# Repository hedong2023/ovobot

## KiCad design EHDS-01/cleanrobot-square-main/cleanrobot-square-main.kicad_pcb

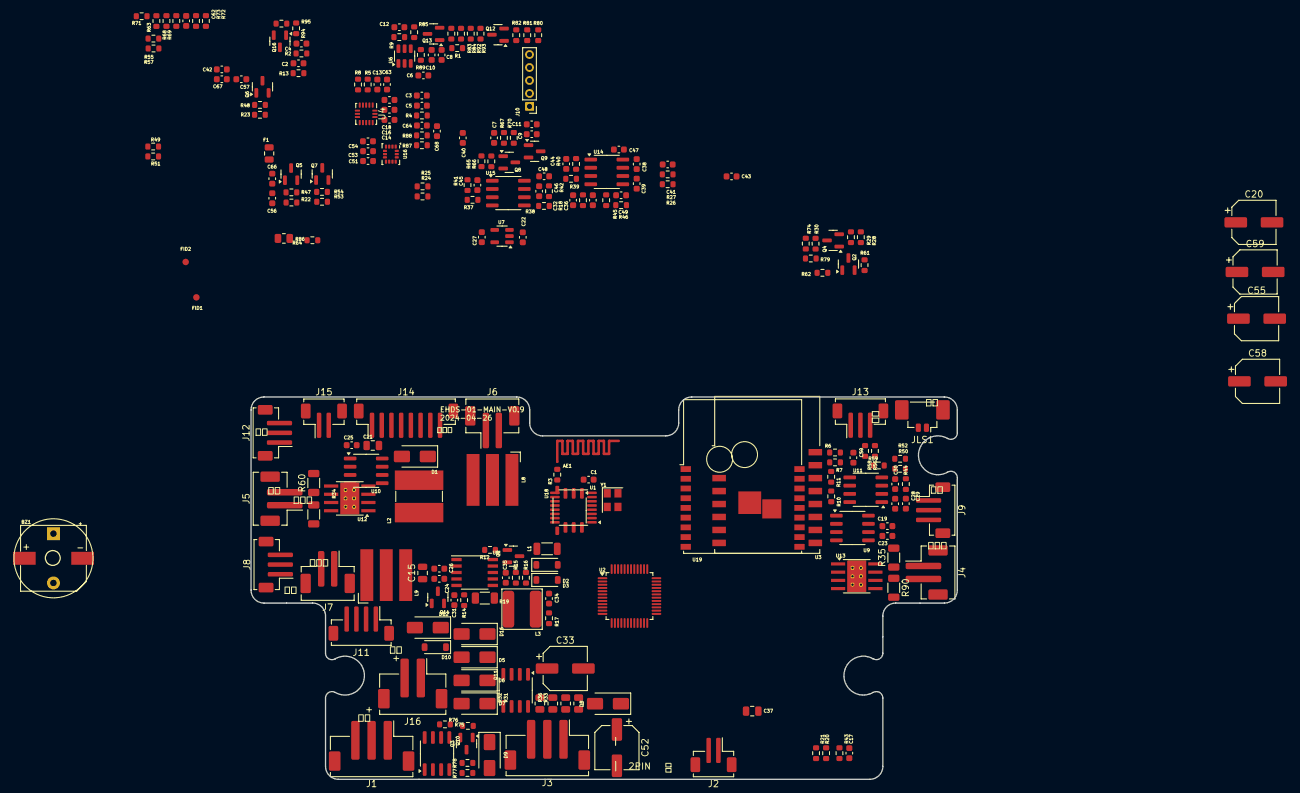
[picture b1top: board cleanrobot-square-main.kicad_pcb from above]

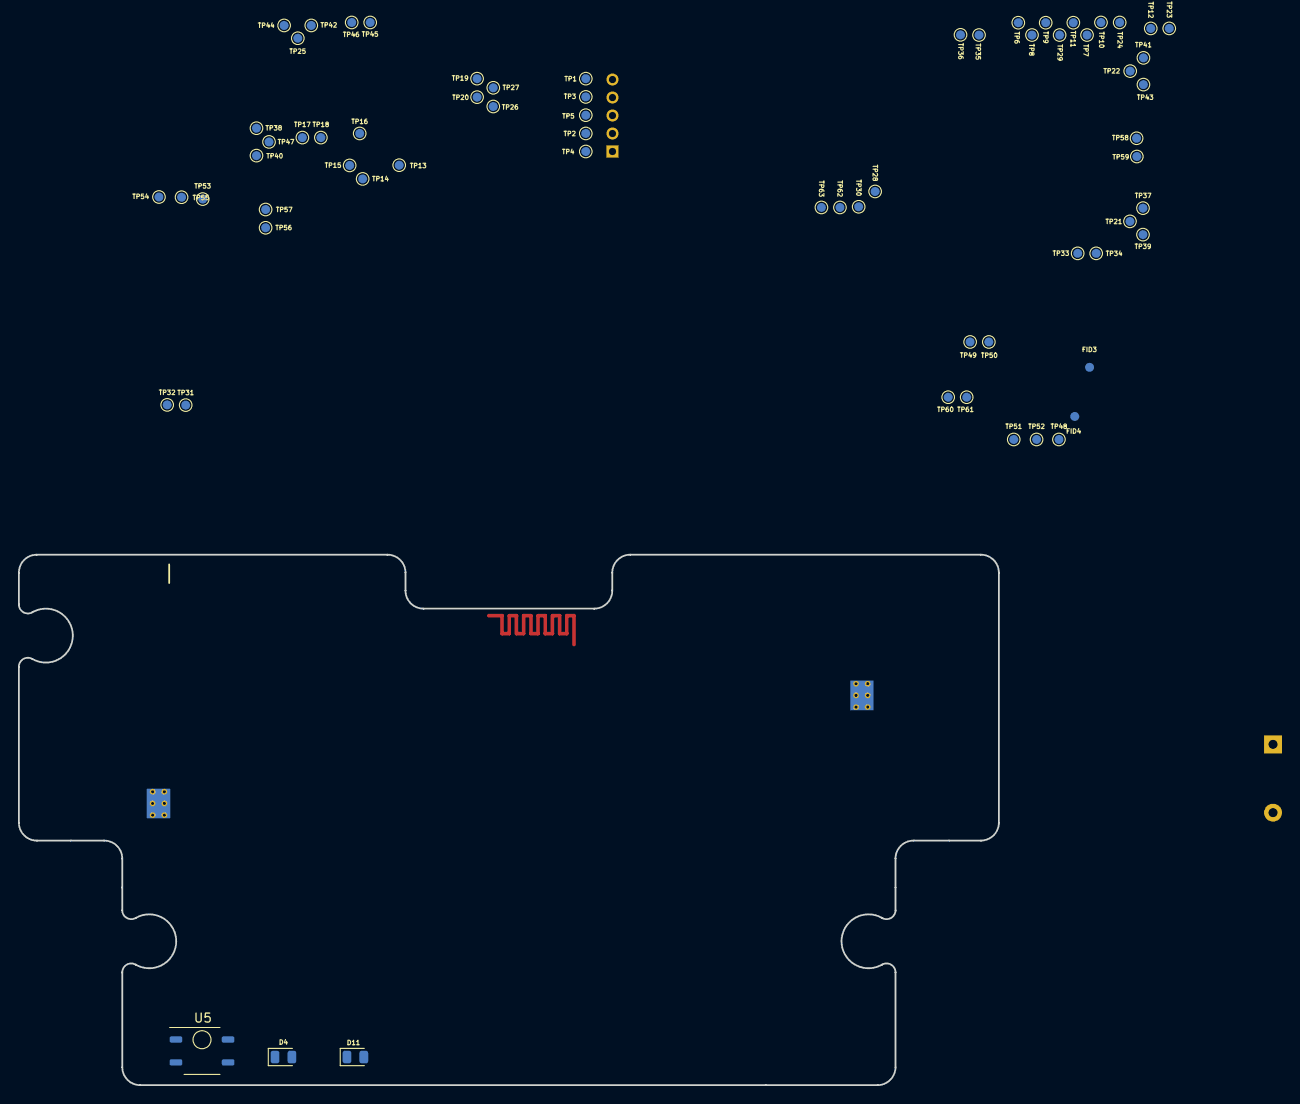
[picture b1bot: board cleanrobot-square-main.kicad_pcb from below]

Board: 2 copper layers, 109.0 x 59.0 mm, 299 parts (68 on the bottom side), 144 nets, no tracks yet.

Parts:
AE1: Antenna; Ovo_PA2401_2.4GHz_Right
BZ1: 85dB/5V; Buzzer_12x9.5RM7.6
BZ2: 85dB/5V 10x9.6x5.5mm; Buzzer_10x9.6x5.5_SMD
C1, C2, C9, C22, C25, C27, C28, C30, C32, C36, C50, C56, C57, C68: 1uF; C_0603_1608Metric
C3, C4, C5, C6, C7, C8, C11, C12, C16, C17, C24, C26, C38, C40, C41, C42, C43, C44, C45, C46, C47, C48, C49, C53, C62, C63, C64, C66, C67: 0.1uF; C_0603_1608Metric
C10: 4.7uF; C_0603_1608Metric
C13, C39, C51: 10nF; C_0603_1608Metric
C14, C29: 0.47uF; C_0603_1608Metric
C15, C21, C37: 10uF/35V; C_0805_2012Metric
C18, C54: 2.2uF; C_0603_1608Metric
C19: 10uF; C_0603_1608Metric
C20, C59: 220uF/10V 6.3x5.4; CP_Elec_6.3x5.4
C23, C34: 1nF; C_0603_1608Metric
C31: 220nF; C_0603_1608Metric
C33, C52, C55, C58: 100uF/35V 6.3x5.4; CP_Elec_6.3x5.4
C35: 1.5pF; C_0603_1608Metric
D1, D5, D6, D7: SS34; D_SMA
D2, D3, D10: SS14; D_SOD-123
D4: BLUE; LED_0805_2012Metric
D8, D9: 1N4004; D_SMA
D11: RED; LED_0805_2012Metric
D12, D16: SMAJ24CA; D_SMA
F1: MF-PSMF050X; Fuse_0805_2012Metric
FID1, FID2, FID3, FID4: Fiducial; Fiducial_1mm_Mask2mm
J1, J3: XH2.54MM/3AWSMT; JST_XHB_B3B-XHB-SM4-TB_1x03-1MP_P2.50mm_Vertical
J2, J15: ZH1.5MM/2ASMT; JST_ZH_B2B-ZR-SM4-TF_1x02-1MP_P1.50mm_Vertical
J4, J5, J6, J7: PH2.0MM/2ASMT; JST_PH_B2B-PH-SM4-TB_1x02-1MP_P2.00mm_Vertical
J8, J9, J12, J13: ZH1.5MM/3ASMT; JST_ZH_B3B-ZR-SM4-TF_1x03-1MP_P1.50mm_Vertical
J10: Conn_01x05; PinHeader_1x05_P2.00mm_Vertical
J11: ZH1.5MM/4ASMT; JST_ZH_B4B-ZR-SM4-TF_1x04-1MP_P1.50mm_Vertical
J14: ZH1.5MM/8ASMT; JST_ZH_B8B-ZR-SM4-TF_1x08-1MP_P1.50mm_Vertical
J16: XHB2.54MM/2ASMT; JST_XHB_B2B-XHB-SM4-TB_1x02-1MP_P2.50mm_Vertical
JLS1: 1.25MM/2ASMT; Molex_PicoBlade_53398-0271_1x02-1MP_P1.25mm_Vertical
L1: 120R@100MHz/3A; L_1206_3216Metric
L2: 68uH; L_GZJ_CD75
L3: 100uH; L_GZJ_WNR6045
L8, L9: 10/500uH; L_WLJ_CD0805
Q1: HSS6107; SOT-23
Q2, Q3, Q4, Q7, Q8, Q9, Q12: SS8050; SOT-23
Q5, Q6: CJ2310; SOT-23
Q10, Q11: NCE4435; SOIC-8_3.9x4.9mm_P1.27mm
Q13, Q16: SI2309; SOT-23
Q14: SI2302; SOT-23
R1, R9, R11, R29, R43, R44, R45, R47, R48, R51, R52, R54, R57, R58, R59, R63, R64, R66, R70, R71, R72, R73, R76, R77, R78, R80, R82, R89, R92, R94: 10K/1%; R_0603_1608Metric
R2, R3, R4, R6, R7, R10, R13, R18, R79, R85: 0R; R_0603_1608Metric
R5, R8: 4.7K/1%; R_0603_1608Metric
R12: 51R; R_0603_1608Metric
R14: 120R; R_0603_1608Metric
R15: 1.5M/1%; R_0603_1608Metric
R16: 120K/1%; R_0603_1608Metric
R17: 100R; R_0603_1608Metric
R19: 0.5R/1%; R_1206_3216Metric
R20, R21, R68, R69: 330R; R_0603_1608Metric
R22, R23, R28, R53, R65, R67, R75, R81: 1K; R_0603_1608Metric
R24, R87: 1M/1%; R_0603_1608Metric
R25, R83, R84, R88: 100K/1%; R_0603_1608Metric
R26: 6.8K/1%; R_0603_1608Metric
R27: 3.3K/1%; R_0603_1608Metric
R30, R74: 680R; R_0603_1608Metric
R31, R32, R33, R36: 0.1R; R_0805_2012Metric
R34, R35, R60, R90: 0.068R/1%(333.333mW); R_1206_3216Metric
R37, R38, R39: 15K/1%; R_0603_1608Metric
R40, R41, R42: 51K/1%; R_0603_1608Metric
R46: 2K/1%; R_0603_1608Metric
R49, R50, R55, R56, R61, R62: 470R; R_0603_1608Metric
R86: 0R; R_0805_2012Metric
R93: 1.6K/1%; R_0603_1608Metric
R95: 30K/5%; R_0603_1608Metric
TP1: RX; TestPoint_Pad_D1.0mm
TP2: SWD; TestPoint_Pad_D1.0mm
TP3: SWC; TestPoint_Pad_D1.0mm
TP4, TP17, TP27, TP29, TP63: 3V3; TestPoint_Pad_D1.0mm
TP5, TP18, TP21, TP22, TP23, TP24, TP25, TP26, TP47, TP48, TP60, TP61, TP62: GND; TestPoint_Pad_D1.0mm
TP6: VPP; TestPoint_Pad_D1.0mm
TP7: LED_RED; TestPoint_Pad_D1.0mm
TP8: CHG_ON_LED; TestPoint_Pad_D1.0mm
TP9: CHG_DONE_LED; TestPoint_Pad_D1.0mm
TP10: IR_OUT; TestPoint_Pad_D1.0mm
TP11: LED_BLUE; TestPoint_Pad_D1.0mm
TP12: START; TestPoint_Pad_D1.0mm
TP13: DO; TestPoint_Pad_D1.0mm
TP14: CLK; TestPoint_Pad_D1.0mm
TP15: DI; TestPoint_Pad_D1.0mm
TP16: CS; TestPoint_Pad_D1.0mm
TP19: RXD; TestPoint_Pad_D1.0mm
TP20: TXD; TestPoint_Pad_D1.0mm
TP28: SCL1; TestPoint_Pad_D1.0mm
TP30: SDA1; TestPoint_Pad_D1.0mm
TP31: WATER_DET_P; TestPoint_Pad_D1.0mm
TP32: WATER_DET_N; TestPoint_Pad_D1.0mm
TP33: SPRAY_BACK_P; TestPoint_Pad_D1.0mm
TP34: SPRAY_BACK_N; TestPoint_Pad_D1.0mm
TP35: SPRAY_FRONT_P; TestPoint_Pad_D1.0mm
TP36: SPRAY_FRONT_N; TestPoint_Pad_D1.0mm
TP37: EDGE_DET_LB_OUT; TestPoint_Pad_D1.0mm
TP38: EDGE_DET_RB; TestPoint_Pad_D1.0mm
TP39: EDGE_DET_LB; TestPoint_Pad_D1.0mm
TP40: EDGE_DET_RB_OUT; TestPoint_Pad_D1.0mm
TP41: EDGE_DET_LT_OUT; TestPoint_Pad_D1.0mm
TP42: EDGE_DET_RT; TestPoint_Pad_D1.0mm
TP43: EDGE_DET_LT; TestPoint_Pad_D1.0mm
TP44: EDGE_DET_RT_OUT; TestPoint_Pad_D1.0mm
TP45: SPEAKER_P; TestPoint_Pad_D1.0mm
TP46: SPEAKER_N; TestPoint_Pad_D1.0mm
TP49, TP50: 24V; TestPoint_Pad_D1.0mm
TP51: BATT; TestPoint_Pad_D1.0mm
TP52: TEMP; TestPoint_Pad_D1.0mm
TP53: VDD; TestPoint_Pad_D1.0mm
TP54: FAN_PWM; TestPoint_Pad_D1.0mm
TP55: FAN_OUT_N; TestPoint_Pad_D1.0mm
TP56: R_MOTOR_OUT+; TestPoint_Pad_D1.0mm
TP57: R_MOTOR_OUT-; TestPoint_Pad_D1.0mm
TP58: L_MOTOR_OUT+; TestPoint_Pad_D1.0mm
TP59: L_MOTOR_OUT-; TestPoint_Pad_D1.0mm
U1: LT8920; TSSOP-16_4.4x5mm_P0.65mm
U2: MM32F0144C6P; LQFP-48_7x7mm_P0.5mm
U3: BT3L; Tuya_BT3L
U4: MPU-6887P; TDK_LGA-16_3x3mm_P0.5mm_LayoutBorder3x5y
U5: IRM-3640CF45; Everlight_IRM-H638T
U6: PMS150C-U06(0xD407B2); SOT-23-6
U7: RT9013-33; SOT-23-5
U8: CN3765; SSOP-10_3.9x4.9mm_P1.00mm
U9: WT588F02B-8S-B2(EHDS-01); SOIC-8_3.9x4.9mm_P1.27mm
U10: XL1509-5.0E1; SOIC-8_3.9x4.9mm_P1.27mm
U11: 8002A; SOIC-8_3.9x4.9mm_P1.27mm
U12, U13: DRV8870DDAR; Texas_HTSOP-8-1EP_3.9x4.9mm_P1.27mm_EP2.95x4.9mm_Mask2.4x3.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
U14, U15: LMV358TP-SR; SOIC-8_3.9x4.9mm_P1.27mm
U16: LSM6DSR; LGA-14_3x2.5mm_P0.5mm_LayoutBorder3x4y
U18: GH6220B; SOIC-8_3.9x4.9mm_P1.27mm
U19: WBR1; Tuya_WBR1
Y1: 12MHz/22pF(10ppm); Oscillator_SMD_Abracon_ASE-4Pin_3.2x2.5mm

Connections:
+3.3VA: C36.1, C47.1, C48.1, R18.2, R45.1, U14.8 (V+), U15.8 (V+)
+3.3VDAC: C4.1, R2.2, U1.12 (LDO_IN), U18.8 (VDD)
+3.3VP: C2.1, C9.1, C11.1, R2.1, R13.2, R80.2, U3.8 (VDD_BAT), U19.1 (VCC), U19.4 (3V3)
+3V3: C6.2, C7.2, C8.2, C10.2, C12.1, C13.2, C16.2, C17.1, C18.2, C19.1, C27.1, C32.1, C51.2, C53.2, C54.2, C62.1, D4.2 (A), D11.2 (A), J10.1, J11.1, J14.4, Q2.3 (C), R4.2, R5.2, R8.2, R9.1, R13.1, R18.1, R26.1, R43.1, R49.1, R50.1, R51.1, R52.1, R55.1, R56.1, R57.1, R58.1, R62.1, R63.2, R64.1, R71.1, R89.1, TP4.1, TP17.1, TP27.1, TP29.1, TP63.1, U2.1 (VDD), U2.24 (VDD), U2.48 (VDD), U4.1 (VDDIO), U4.5 (CS), U4.16 (VDD), U5.3 (Vs), U6.5 (VDD), U7.5 (VOUT), U9.6 (VDD), U16.5 (VDDIO), U16.8 (VDD), U16.12 (CS)
+5V: BZ1.1 (-), BZ2.1 (-), C20.1, C22.1, C50.1, F1.1, L2.2, U7.1 (VIN), U7.3 (EN), U10.3 (FB), U11.6 (VDD)
+24V: D5.2 (A), D6.2 (A), D10.2 (A), J16.1, TP49.1, TP50.1
+BATT: J1.3, Q10.1 (S), Q10.2 (S), Q10.3 (S), R77.2, TP51.1
/driver/L_MOTOR_OUT+: J5.1, TP58.1, U12.6 (OUT1)
/driver/L_MOTOR_OUT-: J5.2, TP59.1, U12.8 (OUT2)
/driver/R_MOTOR_OUT+: J4.1, TP56.1, U13.6 (OUT1)
/driver/R_MOTOR_OUT-: J4.2, TP57.1, U13.8 (OUT2)
/driver/VREF55: C38.1, C39.1, U14.3 (+), U14.6 (-), U14.7, U15.3 (+), U15.5 (+)
/main/6220_ANT: R3.1, U1.9 (ANTB), U18.4 (ANT)
/main/6220_XC1: U1.7 (XTALI), U18.1 (XC1), Y1.1
/main/6220_XC2: U1.6 (XTALO), U18.2 (XC2), Y1.3
/main/BLE_MCU_RXD: R6.2, U2.43 (PB7)
/main/BLE_MCU_TXD: R7.2, U2.42 (PB6)
/main/MISO: U1.2 (MISO), U2.40 (PB4)
/main/MOSI: U1.1 (MOSI), U2.41 (PB5), U18.7 (DATA/MOSI)
/main/RF_REST: U1.4 (~RST), U2.6 (PF1)
/main/SCK: U1.16 (SCK), U2.39 (PB3), U18.6 (SCK)
/main/SCS: U1.14 (SS), U2.5 (PF0), U18.5 (CSN)
/main/TSD_DATA: U2.3 (PC14), U6.3 (PA6)
/main/WIFI_MCU_RXD: R6.1, TP19.1, U3.16 (TL_B1), U19.2 (TX)
/main/WIFI_MCU_TXD: R7.1, TP20.1, U3.15 (TL_B7), U19.3 (RX)
/peripheral/BLUE: Q9.3 (C), R21.1, R69.1
/peripheral/CHG_ON_LED_K: J14.2, Q16.2 (S), TP8.1
/peripheral/RED: Q8.3 (C), R20.1, R68.1
/peripheral/VOICE_BUSY: R11.1, TP16.1, U9.1 (PC2/CS)
/power/BATT_CHRG: C35.1, C37.1, D7.2 (A), Q10.5 (D), Q10.6 (D), Q10.7 (D), Q10.8 (D), R15.1, R19.2, R87.1, U8.7 (BAT)
ADC_BATT: C64.1, R87.2, R88.1, U2.10 (PA0)
ADC_FAN_MOTOR: C44.2, R40.2, U2.11 (PA1), U14.1
ADC_LEFT_MOTOR: C45.2, R41.2, U2.15 (PA5), U15.1
ADC_RIGHT_MOTOR: C46.2, R42.2, U2.16 (PA6), U15.7
ADC_VDD: C40.1, R24.2, R25.1, U2.17 (PA7)
BATT_ON: R75.2, U2.21 (PB10)
BELL: R53.1, U2.20 (PB2)
CHG_DONE_LED: J14.3, R73.1, TP9.1
CHG_ON_LED: R72.1, R95.1
CHRG_LED: R92.2, R93.2, U2.33 (PA12)
EDGE_DET_LB: J8.3, R51.2, TP39.1, U2.35 (PF6)
EDGE_DET_LT: J12.3, R57.2, TP43.1, U2.36 (PF7)
EDGE_DET_RB: J9.3, R52.2, TP38.1, U2.27 (PB14)
EDGE_DET_RT: J13.3, R58.2, TP42.1, U2.28 (PB15)
EN_CHRG: Q14.1 (G), R89.2, U6.4 (PA5/~PRSTB)
GND: C1.2, C2.2, C3.1, C4.2, C5.1, C6.1, C7.1, C8.1, C9.2, C10.1, C11.2, C12.2, C13.1, C14.1, C15.2, C16.1, C17.2, C18.1, C19.2, C20.2, C21.2, C22.2, C23.2, C24.2, C25.2, C27.2, C28.2, C30.1, C31.2, C32.2, C33.2, C34.2, C36.2, C37.2, C38.2, C39.2, C40.2, C41.2, C42.2, C43.2, C47.2, C48.2, C49.2, C50.2, C51.1, C52.2, C53.1, C54.1, C55.2, C58.2, C62.2, C63.2, C64.2, C68.2, D1.2 (A), D3.2 (A), D9.2 (A), D12.2 (A), D16.2 (A), J1.1, J1.MP (MountPin), J2.MP (MountPin), J3.MP (MountPin), J4.MP (MountPin), J5.MP (MountPin), J8.2, J8.MP (MountPin), J9.2, J9.MP (MountPin), J10.3, J11.4, J11.MP (MountPin), J12.2, J12.MP (MountPin), J13.2, J13.MP (MountPin), J14.8, J14.MP (MountPin), J15.2, J15.MP (MountPin), J16.2, J16.MP (MountPin), JLS1.MP (MountPin), Q3.2 (E), Q4.2 (E), Q7.2 (E), Q8.2 (E), Q9.2 (E), Q12.2 (E), Q14.2 (S), R1.1, R16.2, R25.2, R27.2, R29.1, R31.2, R32.2, R33.2, R34.2, R35.2, R36.2, R46.2, R54.2, R60.2, R61.2, R66.2, R70.2, R76.1, R82.2, R86.1, R88.2, R90.2, R93.1, TP5.1, TP18.1, TP21.1, TP22.1, TP23.1, TP24.1, TP25.1, TP26.1, TP47.1, TP48.1, TP60.1, TP61.1, TP62.1, U1.15 (VSS), U2.8 (VSSA), U2.23 (VSS), U2.47 (VSS), U3.9 (GND), U3.17 (PAD), U4.4 (AD0/SDO), U4.9 (RESV), U4.10 (RESV), U4.11 (RESV), U4.12 (RESV), U4.13 (GND), U4.15 (RECV), U5.2 (GND), U6.2 (GND), U7.2 (GND), U8.2 (GND), U9.8 (GND), U10.4 (EN), U10.5 (GND), U10.6 (GND), U10.7 (GND), U10.8 (GND), U11.7 (GND), U12.1 (GND), U12.9 (GND), U13.1 (GND), U13.9 (GND), U14.4 (V-), U15.4 (V-), U16.1 (SDO/SA0), U16.2 (SDX), U16.3 (SCX), U16.6 (GND), U16.7 (GND), U18.3 (VSS), U19.5 (GND), U19.14 (GND), U19.15 (GND), U19.18 (GND), U19.19 (PAD), Y1.2, Y1.4
GNDA: C56.2, C57.2, C59.2, C66.2, C67.2, J6.MP (MountPin), J7.MP (MountPin), Q5.2 (S), Q6.2 (S), R47.2, R48.2, R86.2
IR_OUT: J14.7, R43.2, R63.1, TP10.1, U2.18 (PB0), U5.1 (OUT)
LED_BLUE: R67.1, U2.25 (PB12)
LED_RED: R65.1, U2.22 (PB11)
unnamed: AE1.1 (A), R3.2
unnamed: BZ1.2 (+), BZ2.2 (+), Q7.3 (C)
unnamed: C29.2, R44.1
unnamed: C31.1, R14.2
unnamed: C34.1, R17.2
unnamed: C56.1, C57.1, C59.1, C66.1, C67.1, F1.2, L8.1, L9.1
unnamed: D1.1 (K), L2.1, U10.2 (OUT)
unnamed: D2.2 (A), L1.2
unnamed: D2.1 (K), D3.1 (K), L3.1, R17.1
unnamed: D4.1 (K), R21.2
unnamed: D8.2 (A), J3.2, R31.1, R32.1, R33.1, R36.1, R39.1, TP55.1
unnamed: D9.1 (K), J3.3, Q11.5 (D), Q11.6 (D), Q11.7 (D), Q11.8 (D), R79.2, TP54.1
unnamed: D11.1 (K), R20.2
unnamed: J2.1, R62.2, TP31.1
unnamed: J2.2, Q2.1 (B), TP32.1
unnamed: J6.1, L8.2, Q5.3 (D), TP34.1
unnamed: J6.2, L8.3, TP33.1
unnamed: J7.1, L9.2, Q6.3 (D), TP36.1
unnamed: J7.2, L9.3, TP35.1
unnamed: J8.1, R49.2, TP37.1
unnamed: J9.1, R50.2, TP40.1
unnamed: J12.1, R55.2, TP41.1
unnamed: J13.1, R56.2, TP44.1
unnamed: J14.5, R69.2, TP11.1
unnamed: J14.6, R68.2, TP7.1
unnamed: JLS1.1, TP46.1, U11.8 (VO2)
unnamed: JLS1.2, R59.2, TP45.1, U11.5 (VO1)
unnamed: L1.1, Q1.3 (D)
unnamed: Q1.1 (G), R12.1
unnamed: Q3.1 (B), R75.1, R76.2
unnamed: Q3.3 (C), R78.1
unnamed: Q4.1 (B), R28.2, R29.2
unnamed: Q4.3 (C), R30.2, R79.1
unnamed: Q5.1 (G), R22.2, R47.1
unnamed: Q6.1 (G), R23.2, R48.1
unnamed: Q7.1 (B), R53.2, R54.1
unnamed: Q8.1 (B), R65.2, R66.1
unnamed: Q9.1 (B), R67.2, R70.1
unnamed: Q10.4 (G), R77.1, R78.2
unnamed: Q11.4 (G), R30.1, R74.2
unnamed: Q12.1 (B), R81.2, R82.1
unnamed: Q12.3 (C), R84.1
unnamed: Q13.1 (G), R83.1, R84.2
unnamed: Q14.3 (D), R14.1, U8.5 (COM)
unnamed: Q16.3 (D), R92.1
unnamed: Q16.1 (G), R94.1, R95.2
unnamed: C1.1, U1.5 (LDO_OUT), U1.8 (PLL_VDD)
unnamed: R1.2, U2.44 (BOOT0)
unnamed: C3.2, U2.7 (NRST)
unnamed: C5.2, R4.1, U2.9 (VDDA)
unnamed: R80.1, U3.3 (EN)
unnamed: C14.2, U4.14 (REGOUT)
unnamed: R9.2, U6.6 (PA3)
unnamed: L3.2, R19.1, U8.8 (CSP)
unnamed: R12.2, U8.10 (DRV)
unnamed: C35.2, R15.2, R16.1, U8.6 (FB)
unnamed: C26.2, U8.1 (VG)
unnamed: R72.2, U8.3 (~CHRG)
unnamed: R73.2, U8.4 (~DONE)
unnamed: R10.2, U9.2 (PC1/SO)
unnamed: TP15.1, U9.3 (PI0/SI)
unnamed: TP14.1, U9.4 (PI1/SCK)
unnamed: C23.1, U9.5 (PWMN)
unnamed: C29.1, U9.7 (PWMP/DAC)
unnamed: C30.2, U11.2 (BYPASS), U11.3 (IN+)
unnamed: R44.2, R59.1, U11.4 (IN-)
unnamed: C28.1, R11.2, U11.1 (~SD)
unnamed: R34.1, R37.1, R60.1, U12.7 (ISEN)
unnamed: C41.1, R26.2, R27.1, U12.4 (VREF), U13.4 (VREF)
unnamed: R35.1, R38.1, R90.1, U13.7 (ISEN)
unnamed: C44.1, R39.2, R40.1, U14.2 (-)
unnamed: C49.1, R45.2, R46.1, U14.5 (+)
unnamed: C45.1, R37.2, R41.1, U15.2 (-)
unnamed: C46.1, R38.2, R42.1, U15.6 (-)
PWM_FAN: R28.1, U2.14 (PA4)
PWM_LEFT1: U2.29 (PA8), U12.3 (IN1)
PWM_LEFT2: U2.30 (PA9), U12.2 (IN2)
PWM_RIGHT1: U2.31 (PA10), U13.3 (IN1)
PWM_RIGHT2: U2.32 (PA11), U13.2 (IN2)
SCL1: J11.2, R5.1, TP28.1, U2.45 (PB8), U4.2 (SCL/SCLK), U16.13 (SCL)
SDA1: J11.3, R8.1, TP30.1, U2.46 (PB9), U4.3 (SDA/SDI), U16.14 (SDA)
SPRAY_BACK: R22.1, U2.13 (PA3)
SPRAY_FRONT: R23.1, U2.12 (PA2)
START: J15.1, R71.2, TP12.1, U2.2 (PC13)
SWCLK: J10.4, TP3.1, U2.37 (PA14)
SWDIO: J10.2, TP2.1, U2.34 (PA13)
SW_LED_POWER: R81.1, U2.26 (PB13)
TEMP: C63.1, J1.2, R64.2, TP52.1, U6.1 (PA4)
UART2_RX: J10.5, TP1.1, U2.38 (PA15)
VCC: C15.1, C24.1, C26.1, D10.1 (K), D12.1 (K), Q1.2 (S), Q13.2 (S), R83.2, R85.2, U8.9 (VCC)
VDD: C21.1, C25.1, C33.1, C42.1, C43.1, C52.1, C55.1, C58.1, D5.1 (K), D6.1 (K), D7.1 (K), D8.1 (K), D16.1 (K), J3.1, Q11.1 (S), Q11.2 (S), Q11.3 (S), R24.1, R74.1, TP53.1, U10.1 (VIN), U12.5 (VM), U13.5 (VM)
VOICE_DATA: R10.1, TP13.1, U2.4 (PC15)
VPP: J14.1, Q13.3 (D), R85.1, R94.2, TP6.1
WATER_DET: C68.1, Q2.2 (E), R61.1, U2.19 (PB1)

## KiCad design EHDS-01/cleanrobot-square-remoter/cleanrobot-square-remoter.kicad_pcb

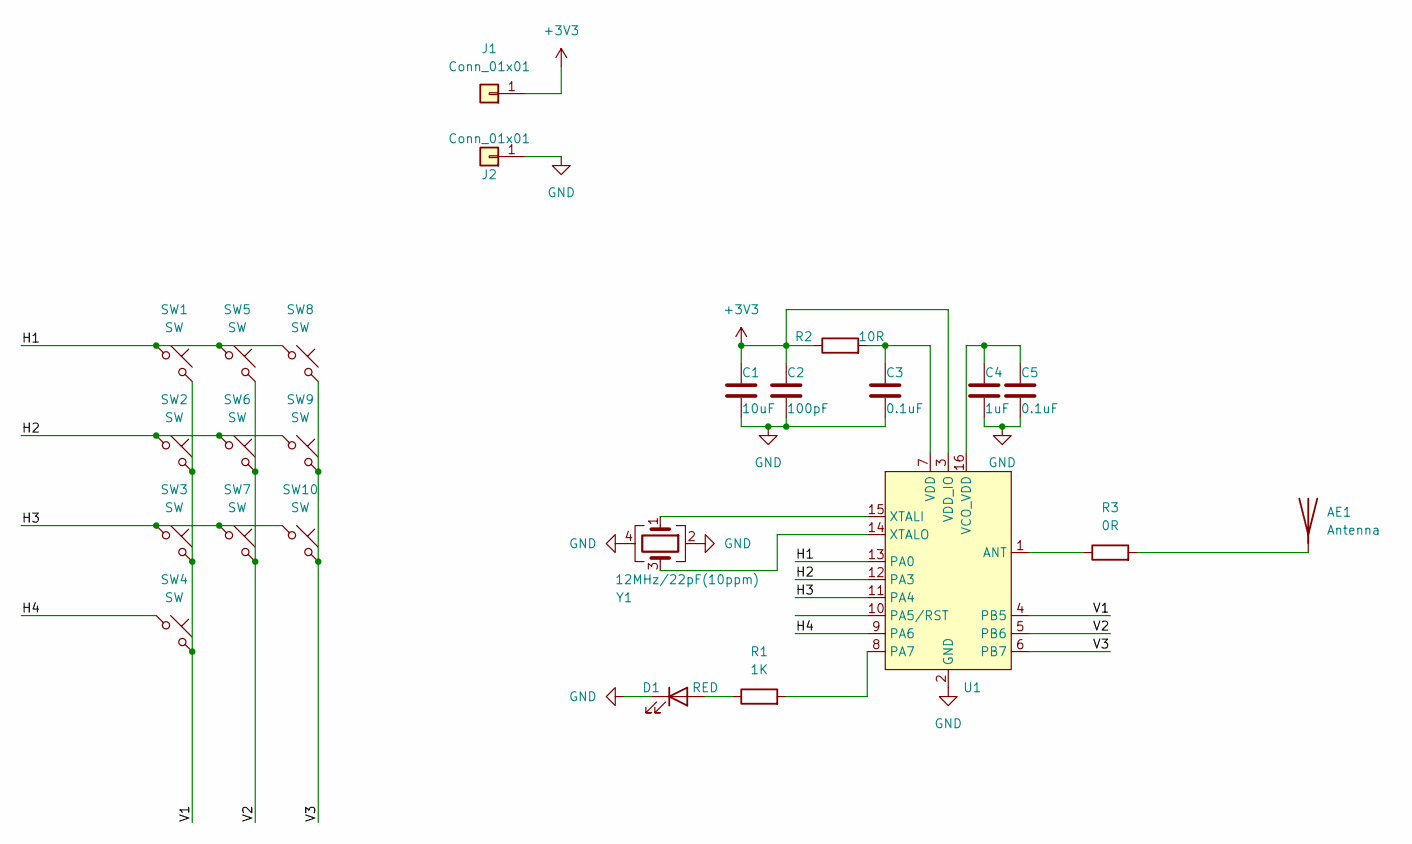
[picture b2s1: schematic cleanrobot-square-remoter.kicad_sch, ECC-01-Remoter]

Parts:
AE1: Antenna; Ovo_PA2401_2.4GHz_Left
C1: 10uF; C_0603_1608Metric
C2: 100pF; C_0603_1608Metric
C3, C5: 0.1uF; C_0603_1608Metric
C4: 1uF; C_0603_1608Metric
D1: RED; LED_D5.0mm
J1, J2: Conn_01x01; Pad_THTPad_4.3x2.1mm_Drill3.1x0.9mm
R1: 1K; R_0603_1608Metric
R2: 10R; R_0603_1608Metric
R3: 0R; R_0603_1608Metric
SW1, SW2, SW3, SW4, SW5, SW6, SW7, SW8, SW9, SW10: SW; Dome_SLICE_6x6mm
U1: SOP-16_3.9x9.9mm_P1.27mm
Y1: 12MHz/22pF(10ppm); Oscillator_SMD_Abracon_ASE-4Pin_3.2x2.5mm

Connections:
+3V3: C1.1, C2.1, J1.1, R2.1, U1.3 (VDD_IO)
/H1: SW1.1, SW5.1, SW8.1, U1.13 (PA0)
/H2: SW2.1, SW6.1, SW9.1, U1.12 (PA3)
/H3: SW3.1, SW7.1, SW10.1, U1.11 (PA4)
/H4: SW4.1, U1.9 (PA6)
/V1: SW1.2, SW2.2, SW3.2, SW4.2, U1.4 (PB5)
/V2: SW5.2, SW6.2, SW7.2, U1.5 (PB6)
/V3: SW8.2, SW9.2, SW10.2, U1.6 (PB7)
GND: C1.2, C2.2, C3.2, C4.2, C5.2, D1.1 (K), J2.1, U1.2 (GND), Y1.2, Y1.4
unnamed: AE1.1 (A), R3.2
unnamed: C3.1, R2.2, U1.7 (VDD)
unnamed: C4.1, C5.1, U1.16 (VCO_VDD)
unnamed: D1.2 (A), R1.1
unnamed: R1.2, U1.8 (PA7)
unnamed: R3.1, U1.1 (ANT)
unnamed: U1.14 (XTALO), Y1.3
unnamed: U1.15 (XTALI), Y1.1

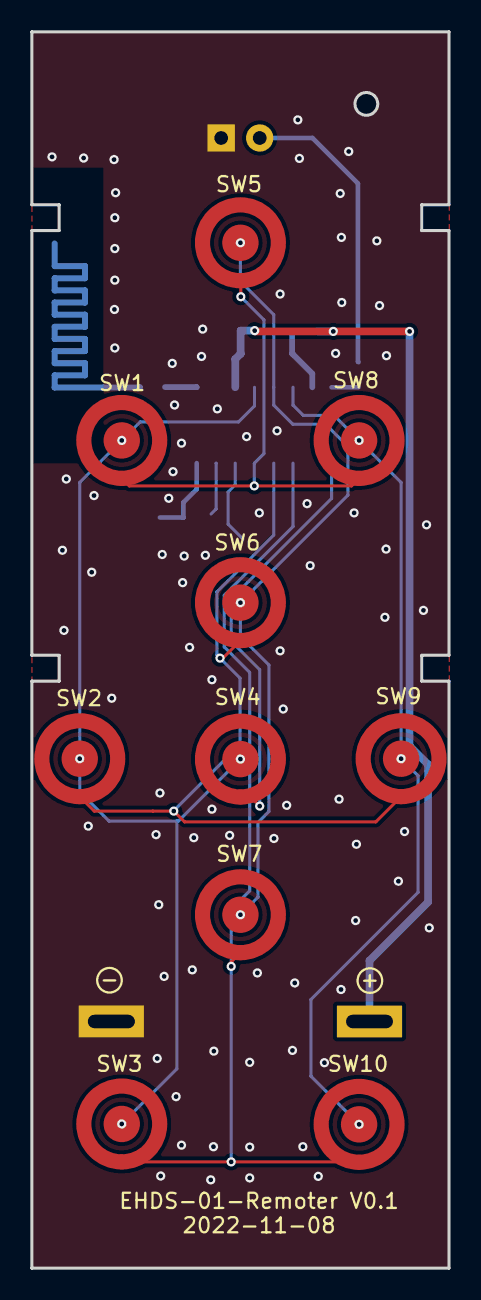
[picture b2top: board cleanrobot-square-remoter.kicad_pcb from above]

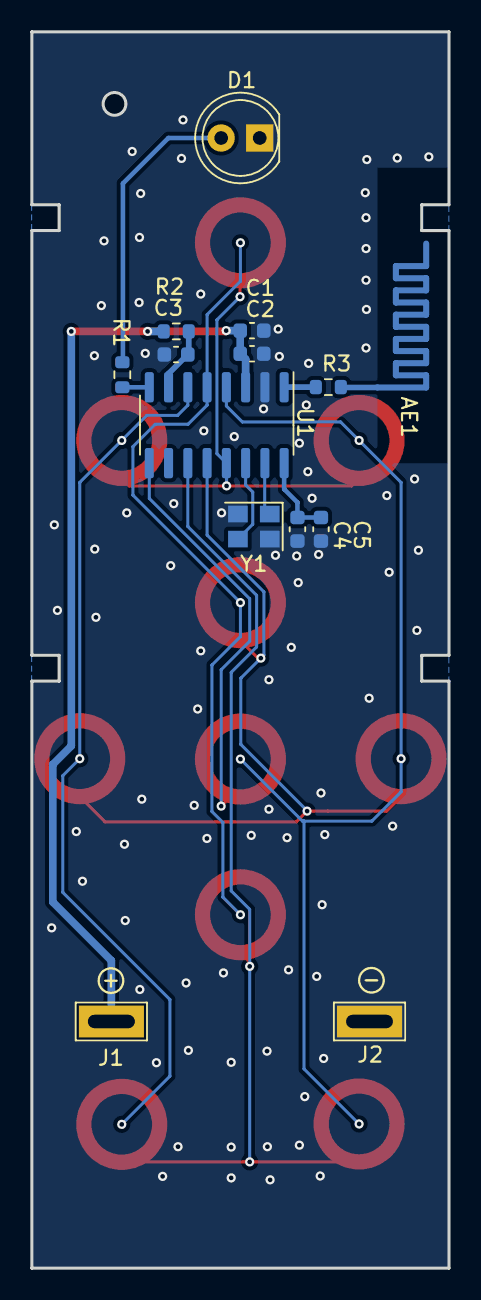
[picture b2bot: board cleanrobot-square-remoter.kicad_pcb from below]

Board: 2 copper layers, 27.5 x 81.5 mm, 24 parts (14 on the bottom side), 17 nets.

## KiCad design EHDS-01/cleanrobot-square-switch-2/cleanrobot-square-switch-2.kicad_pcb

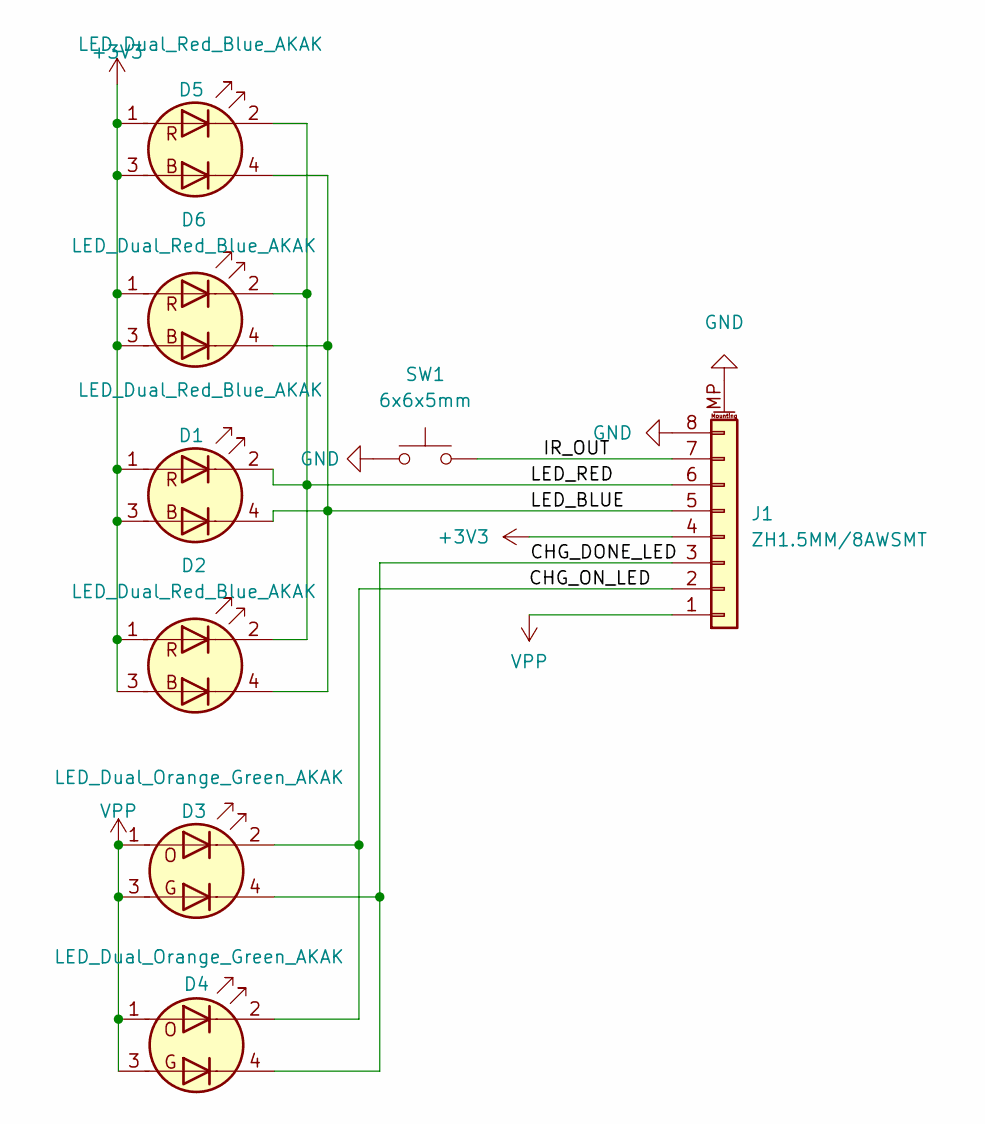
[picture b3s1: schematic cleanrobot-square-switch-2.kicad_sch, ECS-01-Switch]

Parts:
D1, D2, D5, D6: LED_Dual_Red_Blue_AKAK; LED_Dual_1.6x1.5mm
D3, D4: LED_Dual_Orange_Green_AKAK; LED_Dual_1.6x1.5mm
J1: ZH1.5MM/8AWSMT; JST_ZH_S8B-ZR-SM4-TF_1x08-1MP_P1.50mm_Horizontal
SW1: 6x6x5mm; SW_Push_1P1T_NO_6x6mm_H9.5mm

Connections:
+3V3: D1.1 (A1), D1.3 (A2), D2.1 (A1), D2.3 (A2), D5.1 (A1), D5.3 (A2), D6.1 (A1), D6.3 (A2), J1.4
/CHG_DONE_LED: D3.4 (K2), D4.4 (K2), J1.3
/CHG_ON_LED: D3.2 (K1), D4.2 (K1), J1.2
/IR_OUT: J1.7, SW1.2
/LED_BLUE: D1.4 (K2), D2.4 (K2), D5.4 (K2), D6.4 (K2), J1.5
/LED_RED: D1.2 (K1), D2.2 (K1), D5.2 (K1), D6.2 (K1), J1.6
GND: J1.8, J1.MP (MountPin), SW1.1
VPP: D3.1 (A1), D3.3 (A2), D4.1 (A1), D4.3 (A2), J1.1

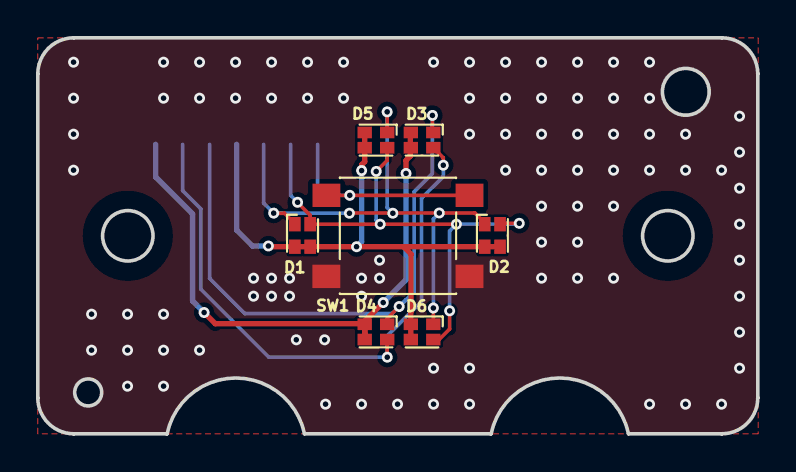
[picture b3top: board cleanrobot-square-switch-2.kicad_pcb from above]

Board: 2 copper layers, 40.0 x 22.0 mm, 8 parts (1 on the bottom side), 8 nets.

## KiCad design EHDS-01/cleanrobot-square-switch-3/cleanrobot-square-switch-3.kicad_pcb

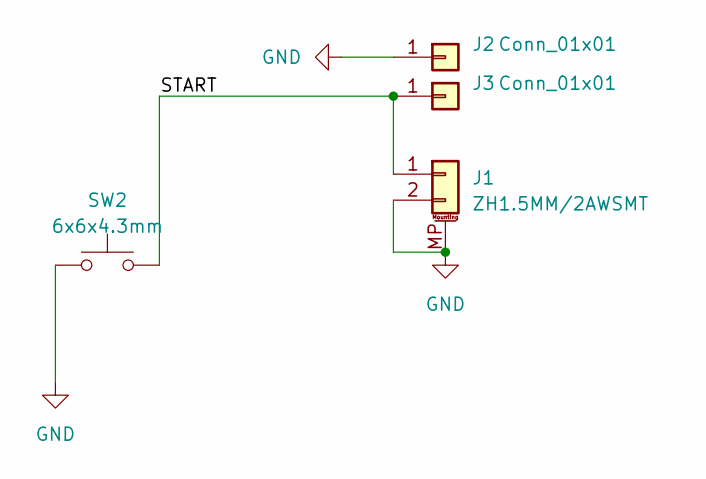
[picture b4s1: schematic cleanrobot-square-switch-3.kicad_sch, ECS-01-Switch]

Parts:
J1: ZH1.5MM/2AWSMT; JST_ZH_S2B-ZR-SM4-TF_1x02-1MP_P1.50mm_Horizontal
J2, J3: Conn_01x01; SolderWire-0.5sqmm_1x01_D0.9mm_OD2.1mm
SW2: 6x6x4.3mm; SW_Push_1P1T_NO_6x6mm_H9.5mm

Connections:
/START: J1.1, J3.1, SW2.2
GND: J1.2, J1.MP (MountPin), J2.1, SW2.1

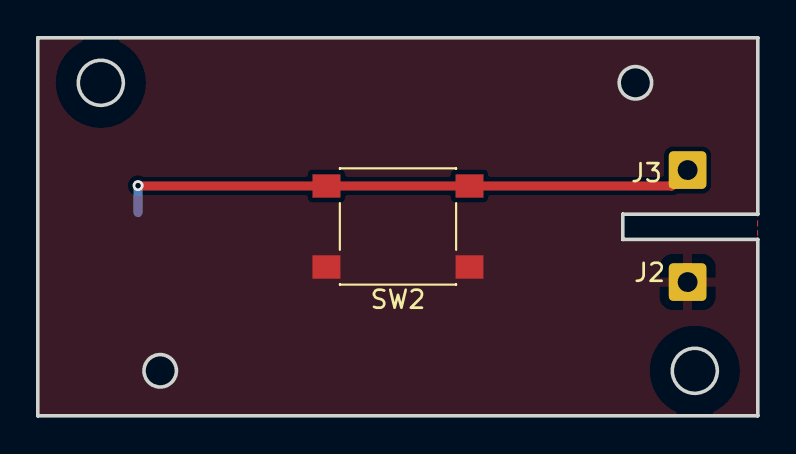
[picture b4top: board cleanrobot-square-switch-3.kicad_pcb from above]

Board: 2 copper layers, 40.0 x 21.0 mm, 4 parts (1 on the bottom side), 2 nets.

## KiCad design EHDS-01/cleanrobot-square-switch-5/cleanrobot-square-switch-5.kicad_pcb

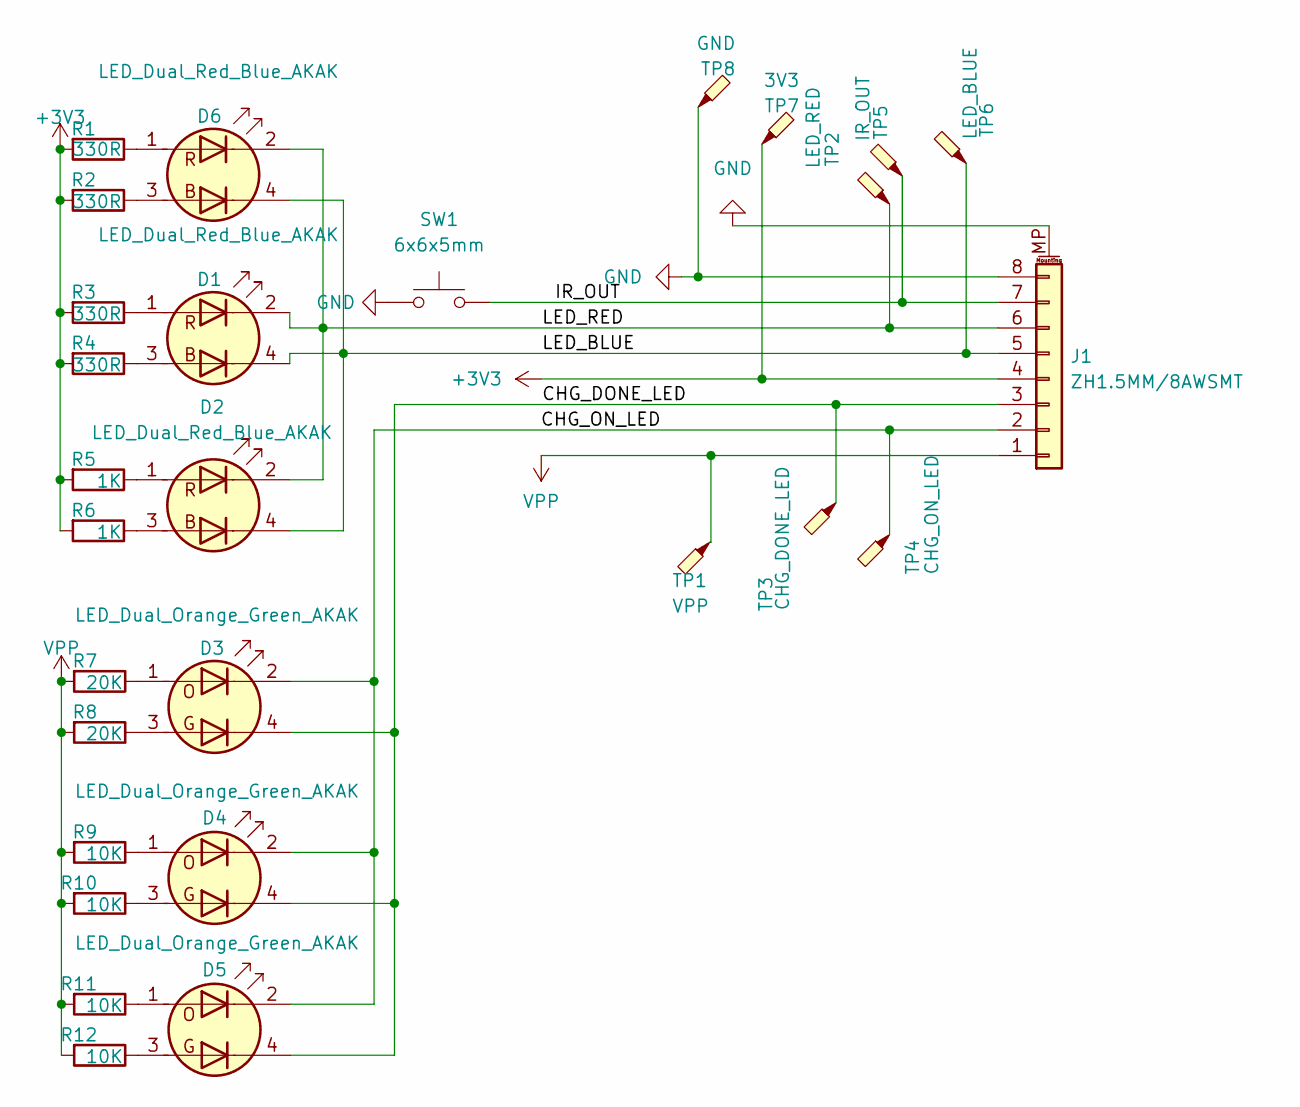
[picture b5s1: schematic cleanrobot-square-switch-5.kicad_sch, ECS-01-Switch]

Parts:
D1, D2, D6: LED_Dual_Red_Blue_AKAK; LED_Dual_1.6x1.5mm
D3, D4, D5: LED_Dual_Orange_Green_AKAK; LED_Dual_1.6x1.5mm
J1: ZH1.5MM/8AWSMT; JST_ZH_S8B-ZR-SM4-TF_1x08-1MP_P1.50mm_Horizontal
R1, R2, R3, R4: 330R; R_0603_1608Metric
R5, R6: 1K; R_0603_1608Metric
R7, R8: 20K; R_0603_1608Metric
R9, R10, R11, R12: 10K; R_0603_1608Metric
SW1: 6x6x5mm; SW_Push_1P1T_NO_6x6mm_H5.0mm
TP1: VPP; TestPoint_Pad_D1.0mm
TP2: LED_RED; TestPoint_Pad_D1.0mm
TP3: CHG_DONE_LED; TestPoint_Pad_D1.0mm
TP4: CHG_ON_LED; TestPoint_Pad_D1.0mm
TP5: IR_OUT; TestPoint_Pad_D1.0mm
TP6: LED_BLUE; TestPoint_Pad_D1.0mm
TP7: 3V3; TestPoint_Pad_D1.0mm
TP8: GND; TestPoint_Pad_D1.0mm

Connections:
+3V3: J1.4, R1.2, R2.2, R3.2, R4.2, R5.2, R6.2, TP7.1
/CHG_DONE_LED: D3.4 (K2), D4.4 (K2), D5.4 (K2), J1.3, TP3.1
/CHG_ON_LED: D3.2 (K1), D4.2 (K1), D5.2 (K1), J1.2, TP4.1
/IR_OUT: J1.7, SW1.2, TP5.1
/LED_BLUE: D1.4 (K2), D2.4 (K2), D6.4 (K2), J1.5, TP6.1
/LED_RED: D1.2 (K1), D2.2 (K1), D6.2 (K1), J1.6, TP2.1
GND: J1.8, J1.MP (MountPin), SW1.1, TP8.1
unnamed: D1.1 (A1), R3.1
unnamed: D1.3 (A2), R4.1
unnamed: D2.1 (A1), R5.1
unnamed: D2.3 (A2), R6.1
unnamed: D3.1 (A1), R7.1
unnamed: D3.3 (A2), R8.1
unnamed: D4.1 (A1), R9.1
unnamed: D4.3 (A2), R10.1
unnamed: D5.1 (A1), R11.1
unnamed: D5.3 (A2), R12.1
unnamed: D6.1 (A1), R1.1
unnamed: D6.3 (A2), R2.1
VPP: J1.1, R7.2, R8.2, R9.2, R10.2, R11.2, R12.2, TP1.1

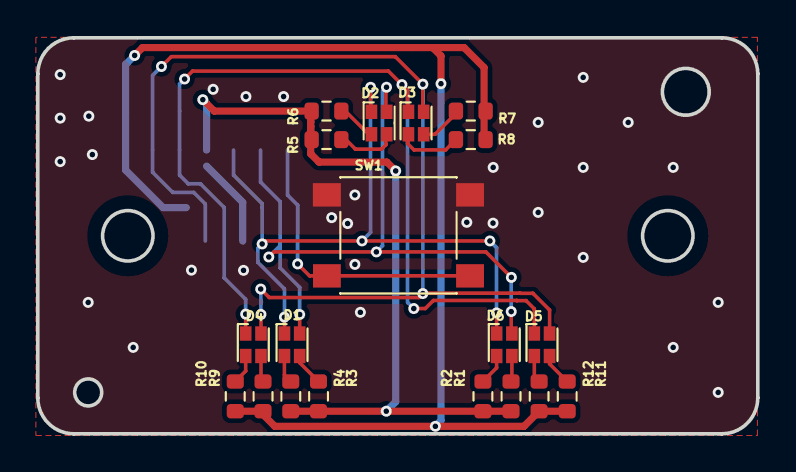
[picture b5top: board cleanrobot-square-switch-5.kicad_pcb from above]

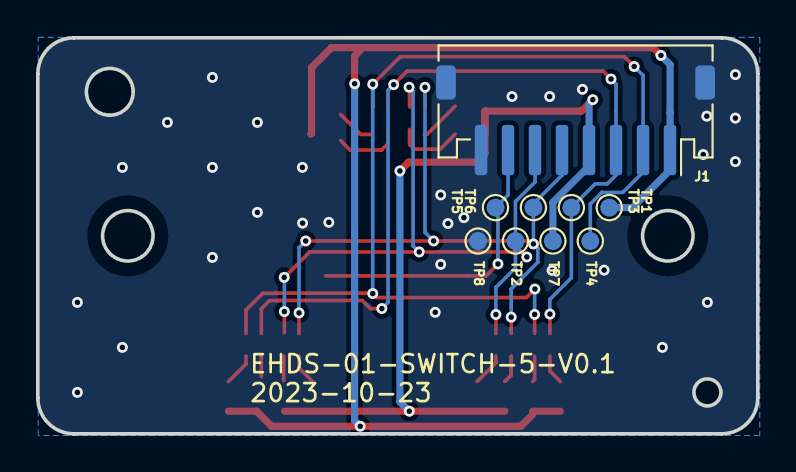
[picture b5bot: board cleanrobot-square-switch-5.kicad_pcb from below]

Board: 2 copper layers, 40.0 x 22.0 mm, 28 parts (9 on the bottom side), 20 nets.

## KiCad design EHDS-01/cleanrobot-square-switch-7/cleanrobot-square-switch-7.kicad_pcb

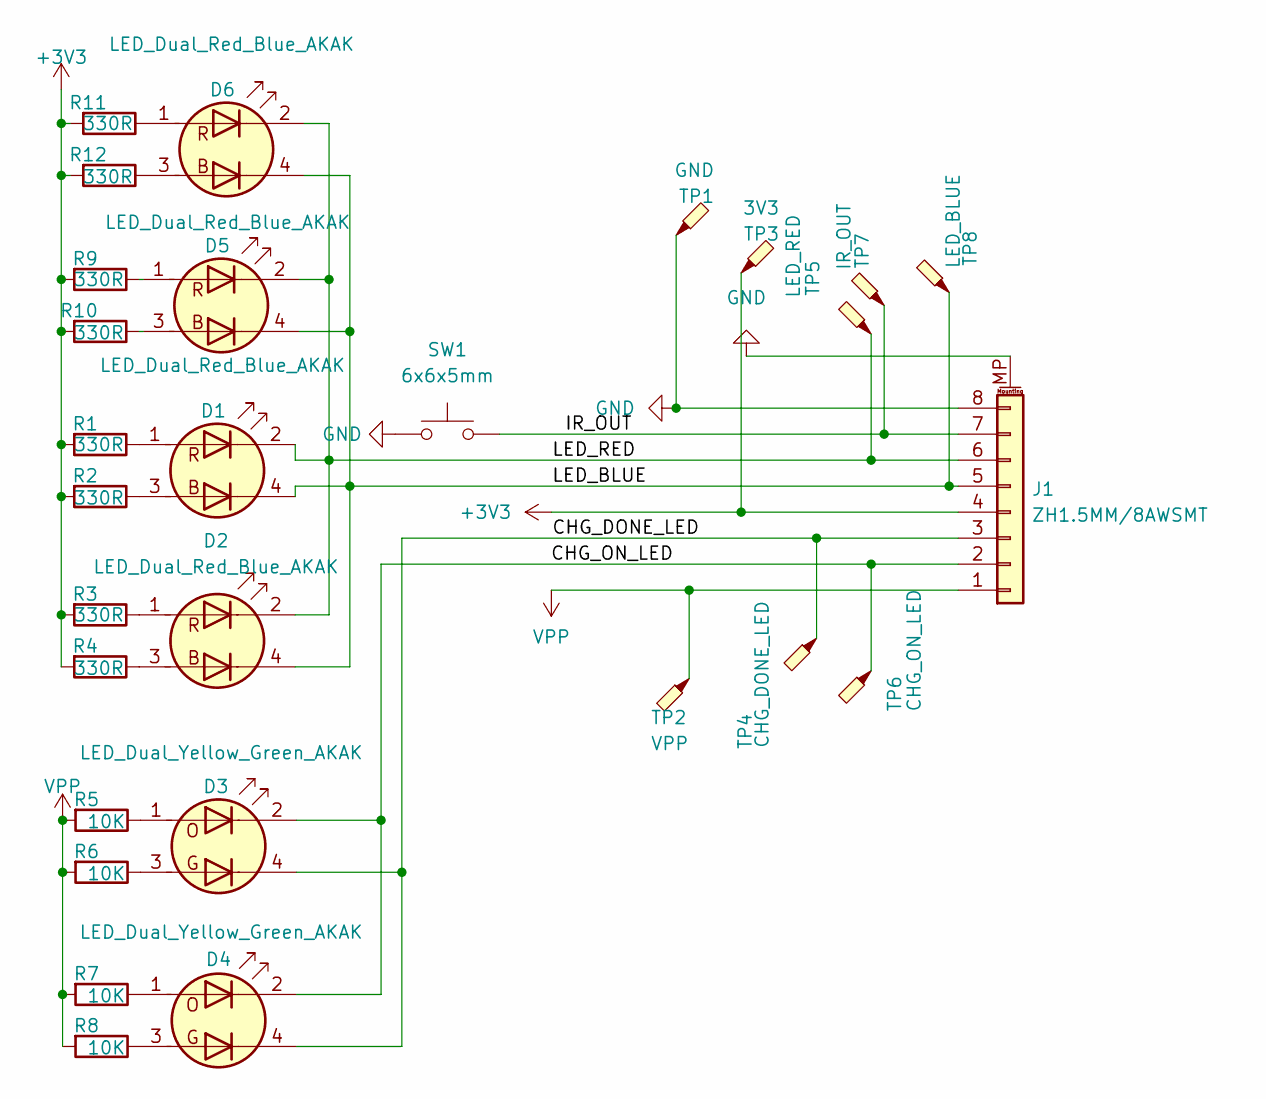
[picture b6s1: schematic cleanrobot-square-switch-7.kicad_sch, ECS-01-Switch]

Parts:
D1, D2, D5, D6: LED_Dual_Red_Blue_AKAK; LED_Dual_1.6x1.5mm
D3, D4: LED_Dual_Yellow_Green_AKAK; LED_Dual_1.6x1.5mm
J1: ZH1.5MM/8AWSMT; JST_ZH_S8B-ZR-SM4-TF_1x08-1MP_P1.50mm_Horizontal
R1, R2, R3, R4, R9, R10, R11, R12: 330R; R_0603_1608Metric
R5, R6, R7, R8: 10K; R_0603_1608Metric
SW1: 6x6x5mm; SW_Push_1P1T_NO_6x6mm_H5.0mm
TP1: GND; TestPoint_Pad_D1.0mm
TP2: VPP; TestPoint_Pad_D1.0mm
TP3: 3V3; TestPoint_Pad_D1.0mm
TP4: CHG_DONE_LED; TestPoint_Pad_D1.0mm
TP5: LED_RED; TestPoint_Pad_D1.0mm
TP6: CHG_ON_LED; TestPoint_Pad_D1.0mm
TP7: IR_OUT; TestPoint_Pad_D1.0mm
TP8: LED_BLUE; TestPoint_Pad_D1.0mm

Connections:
+3V3: J1.4, R1.2, R2.2, R3.2, R4.2, R9.2, R10.2, R11.2, R12.2, TP3.1
/CHG_DONE_LED: D3.4 (K2), D4.4 (K2), J1.3, TP4.1
/CHG_ON_LED: D3.2 (K1), D4.2 (K1), J1.2, TP6.1
/IR_OUT: J1.7, SW1.2, TP7.1
/LED_BLUE: D1.4 (K2), D2.4 (K2), D5.4 (K2), D6.4 (K2), J1.5, TP8.1
/LED_RED: D1.2 (K1), D2.2 (K1), D5.2 (K1), D6.2 (K1), J1.6, TP5.1
GND: J1.8, J1.MP (MountPin), SW1.1, TP1.1
unnamed: D1.1 (A1), R1.1
unnamed: D1.3 (A2), R2.1
unnamed: D2.1 (A1), R3.1
unnamed: D2.3 (A2), R4.1
unnamed: D3.1 (A1), R5.1
unnamed: D3.3 (A2), R6.1
unnamed: D4.1 (A1), R7.1
unnamed: D4.3 (A2), R8.1
unnamed: D5.1 (A1), R9.1
unnamed: D5.3 (A2), R10.1
unnamed: D6.1 (A1), R11.1
unnamed: D6.3 (A2), R12.1
VPP: J1.1, R5.2, R6.2, R7.2, R8.2, TP2.1

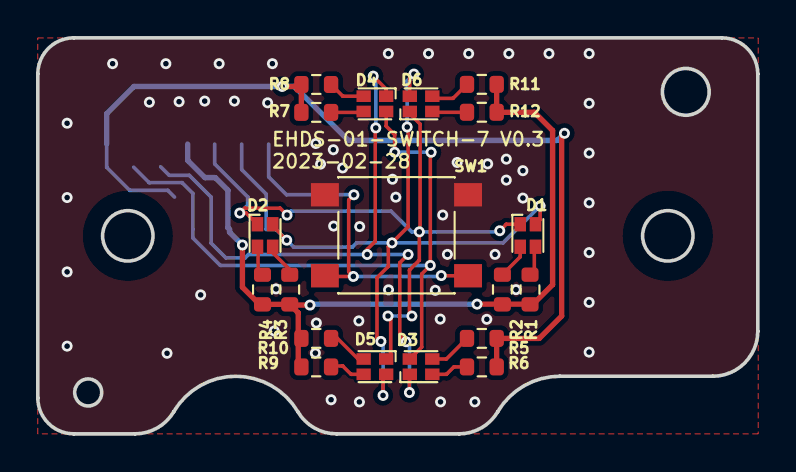
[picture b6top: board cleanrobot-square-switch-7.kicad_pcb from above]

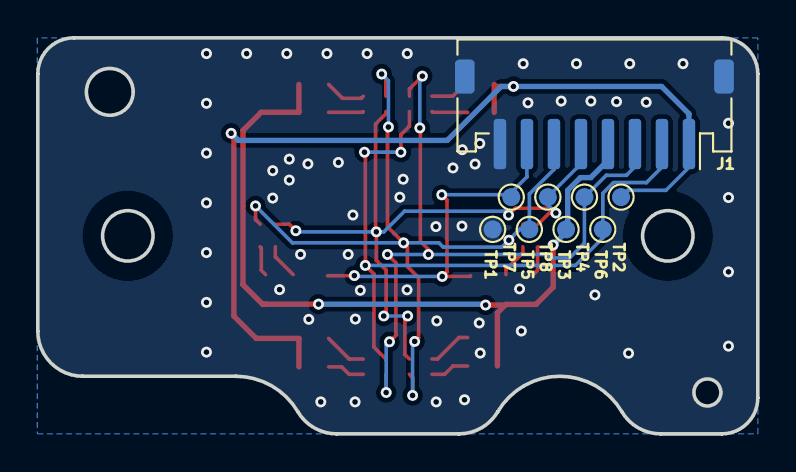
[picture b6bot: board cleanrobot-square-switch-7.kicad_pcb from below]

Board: 2 copper layers, 40.0 x 22.0 mm, 28 parts (9 on the bottom side), 20 nets.
